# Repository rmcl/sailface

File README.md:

# SailFace

An autonomous (non-sail powered) boat thing.

# Photos

## Mark II

## Mark I

# Code organization

## Microcontroller (sailface)

Runs on an arduino MEGA. This code manages navigation, communication and power management.

## Control (sailface_control)

Python code for controling sailface remotely.

### Lambda Data Capture (lambda_data_capture)

This module is a lambda function that will receive the messages relayed from the Iridium Short-Burst Data (SBD) network via the RockBLOCK service (https://docs.rockblock.rock7.com/docs/getting-started). 

### Command Lib (sailface_command)

A python library for creating command messages that can be sent to the vessel.

### Notebooks

Various jupyter notebooks for processing KML + sending commands to the vessel.

## Schematics

PCB/Schematic Designs for an Arduino shield which connects the various electronic components. Created using KiCAD

## 3dmodels

3d models for various parts largely for supporting the internals of the vessel.

# Communication

The Arduino communicates sends messages to the Iridium Short-Burst Data services via a RockBLOCK 9603.

SailFace status messages:

### Power

```
P:<batteryVoltage>,batteryCurrentDraw,solarPanelCurrent
P:3.70,500,400
```

### Navigation/Position

```
N:<positionValid>,<latitude>,<longitude>,<speed>,<course>,<gpsFixAge>
```

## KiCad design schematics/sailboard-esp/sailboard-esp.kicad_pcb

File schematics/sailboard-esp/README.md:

Changelog
##################

Version 1.1
---------------------
* Moved towards using a buck converter from Vin to 5V and then a simple linear regulator for 5v to 3.3v

Version 1.2
------------------
* Added dampening capacitor next to servo.

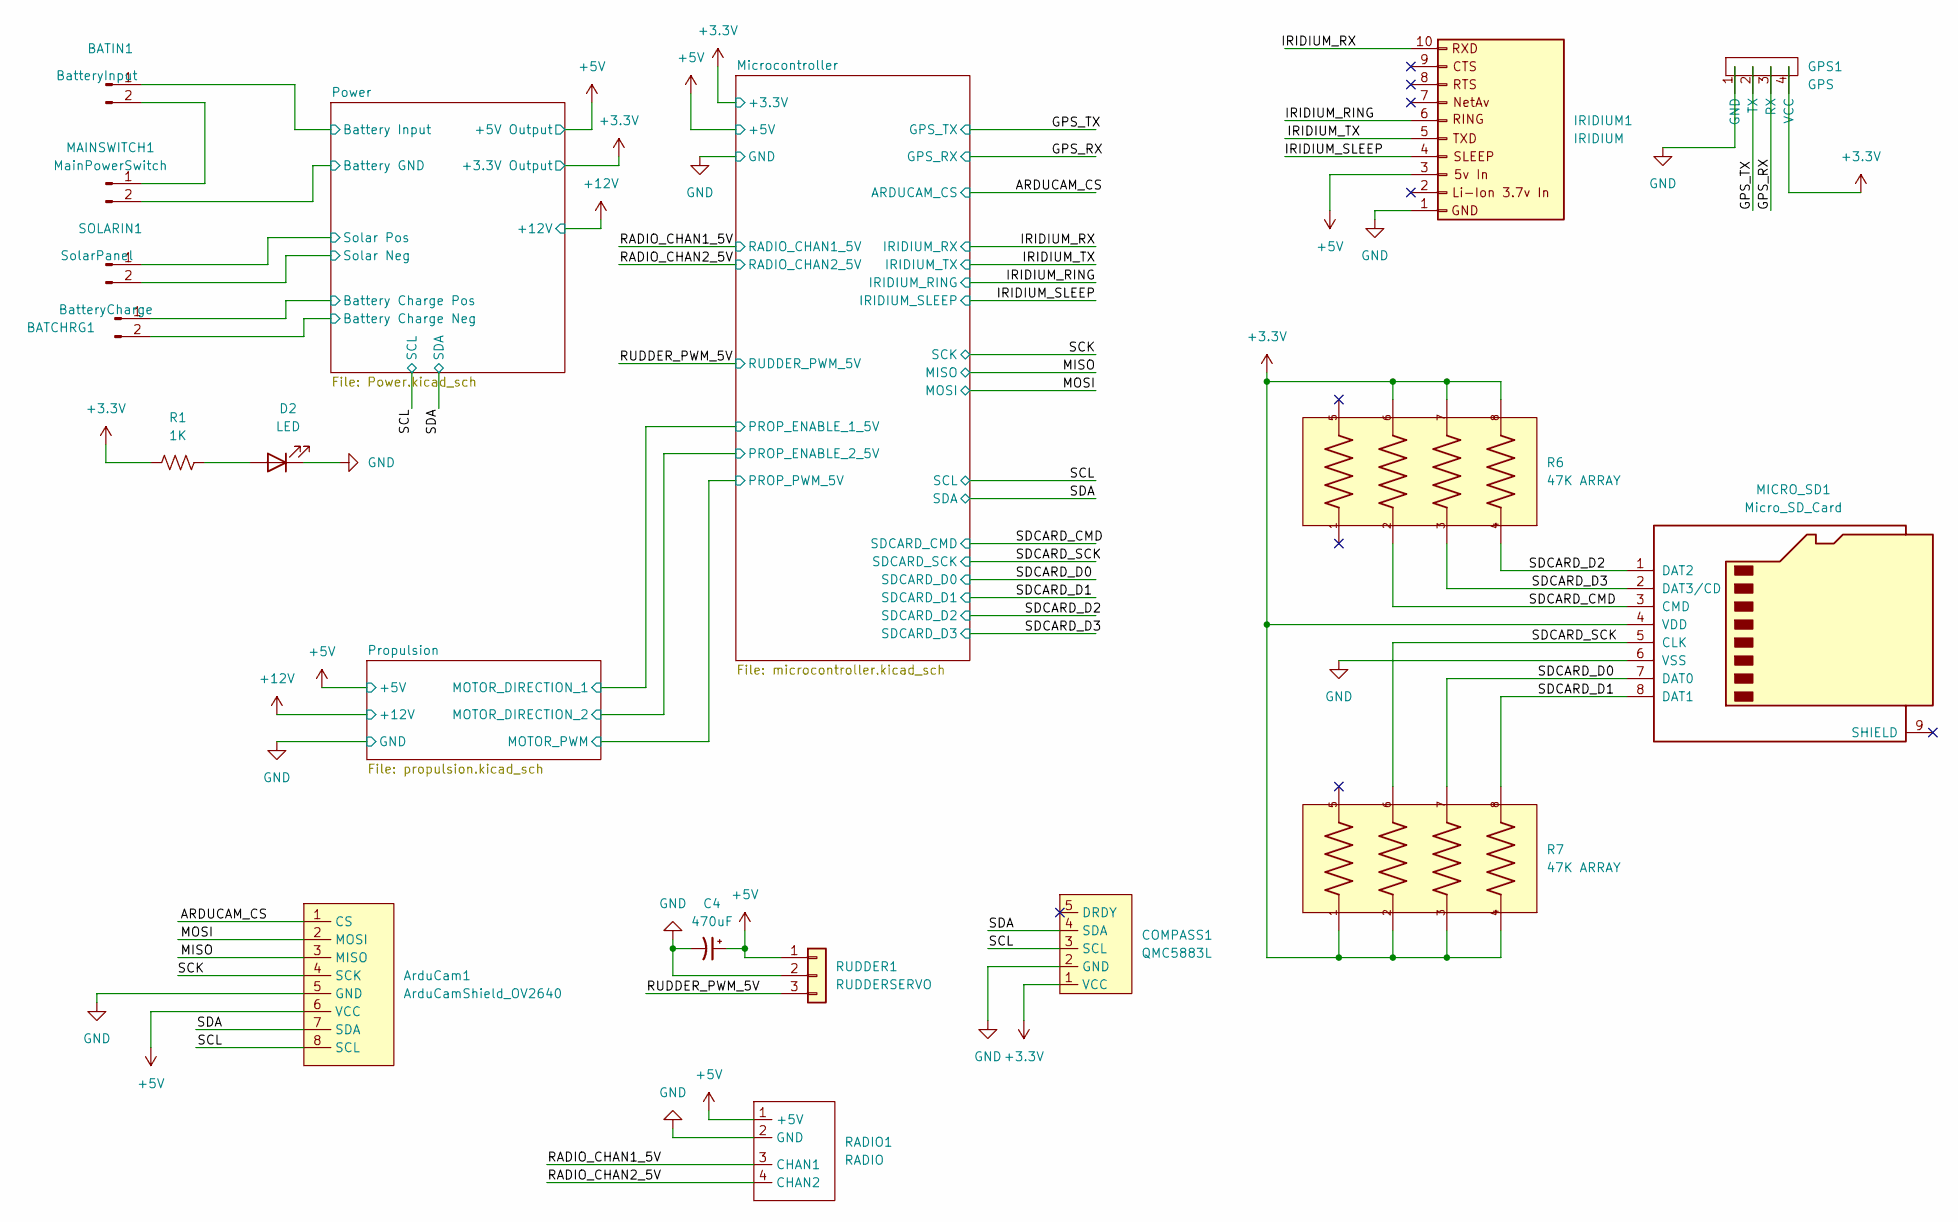
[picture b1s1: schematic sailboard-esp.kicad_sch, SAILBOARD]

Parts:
ArduCam1: ArduCamShield_OV2640; PinHeader_1x08_P2.54mm_Vertical
BATCHRG1: BatteryCharge; JST_XH_B2B-XH-A_1x02_P2.50mm_Vertical
BATIN1: BatteryInput; JST_XH_B2B-XH-A_1x02_P2.50mm_Vertical
C4: 470uF; CP_Radial_D8.0mm_P3.50mm
COMPASS1: QMC5883L; PinHeader_1x05_P2.54mm_Vertical
D2: LED; LED_0603_1608Metric
GPS1: GPS; PinHeader_1x04_P2.54mm_Vertical
IRIDIUM1: IRIDIUM; Molex_PicoBlade_53047-1010_1x10_P1.25mm_Vertical
MAINSWITCH1: MainPowerSwitch; JST_XH_B2B-XH-A_1x02_P2.50mm_Vertical
MICRO_SD1: Micro_SD_Card; microSD_HC_Molex_104031-0811
R1: 1K; R_0603_1608Metric
R6, R7: 47K ARRAY; RESCAXE80P320X160X70-8N; PARTREV 0
RADIO1: RADIO; PinHeader_1x04_P2.54mm_Vertical
RUDDER1: RUDDERSERVO; JST_XH_B3B-XH-A_1x03_P2.50mm_Vertical
SOLARIN1: SolarPanel; JST_XH_B2B-XH-A_1x02_P2.50mm_Vertical

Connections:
+3.3V: COMPASS1.1 (VCC), GPS1.4 (VCC), MICRO_SD1.4 (VDD), R1.1, R6.6, R6.7, R6.8, R7.1, R7.2, R7.3, R7.4; also elsewhere on the board
+5V: ArduCam1.6 (VCC), C4.1, IRIDIUM1.3 (5V), RADIO1.1 (+5V), RUDDER1.1; also elsewhere on the board
/ARDUCAM_CS: ArduCam1.1 (CS); also elsewhere on the board
/GPS_RX: GPS1.3 (RX)
/GPS_TX: GPS1.2 (TX); also elsewhere on the board
/IRIDIUM_RING: IRIDIUM1.6 (RING); also elsewhere on the board
/IRIDIUM_RX: IRIDIUM1.10 (RXD); also elsewhere on the board
/IRIDIUM_SLEEP: IRIDIUM1.4 (SLEEP); also elsewhere on the board
/IRIDIUM_TX: IRIDIUM1.5 (TXD); also elsewhere on the board
/MISO: ArduCam1.3 (MISO); also elsewhere on the board
/MOSI: ArduCam1.2 (MOSI); also elsewhere on the board
/Power/Battery Charge Neg: BATCHRG1.2, SOLARIN1.2
/Power/Battery Charge Pos: BATCHRG1.1; also elsewhere on the board
/Power/Battery Input: BATIN1.1; also elsewhere on the board
/Power/Solar Pos: SOLARIN1.1; also elsewhere on the board
/RADIO_CHAN1_5V: RADIO1.3 (CHAN1); also elsewhere on the board
/RADIO_CHAN2_5V: RADIO1.4 (CHAN2); also elsewhere on the board
/RUDDER_PWM_5V: RUDDER1.3; also elsewhere on the board
/SCK: ArduCam1.4 (SCK); also elsewhere on the board
/SCL: ArduCam1.8 (SCL), COMPASS1.3 (SCL); also elsewhere on the board
/SDA: ArduCam1.7 (SDA), COMPASS1.4 (SDA); also elsewhere on the board
/SDCARD_CMD: MICRO_SD1.3 (CMD), R6.2; also elsewhere on the board
/SDCARD_D0: MICRO_SD1.7 (DAT0), R7.7; also elsewhere on the board
/SDCARD_D1: MICRO_SD1.8 (DAT1), R7.8; also elsewhere on the board
/SDCARD_D2: MICRO_SD1.1 (DAT2), R6.4; also elsewhere on the board
/SDCARD_D3: MICRO_SD1.2 (DAT3/CD), R6.3; also elsewhere on the board
/SDCARD_SCK: MICRO_SD1.5 (CLK), R7.6; also elsewhere on the board
GND: ArduCam1.5 (GND), C4.2, COMPASS1.2 (GND), D2.1 (K), GPS1.1 (GND), IRIDIUM1.1 (GND), MAINSWITCH1.2, MICRO_SD1.6 (VSS), RADIO1.2 (GND), RUDDER1.2; also elsewhere on the board
unnamed: BATIN1.2, MAINSWITCH1.1
unnamed: D2.2 (A), R1.2

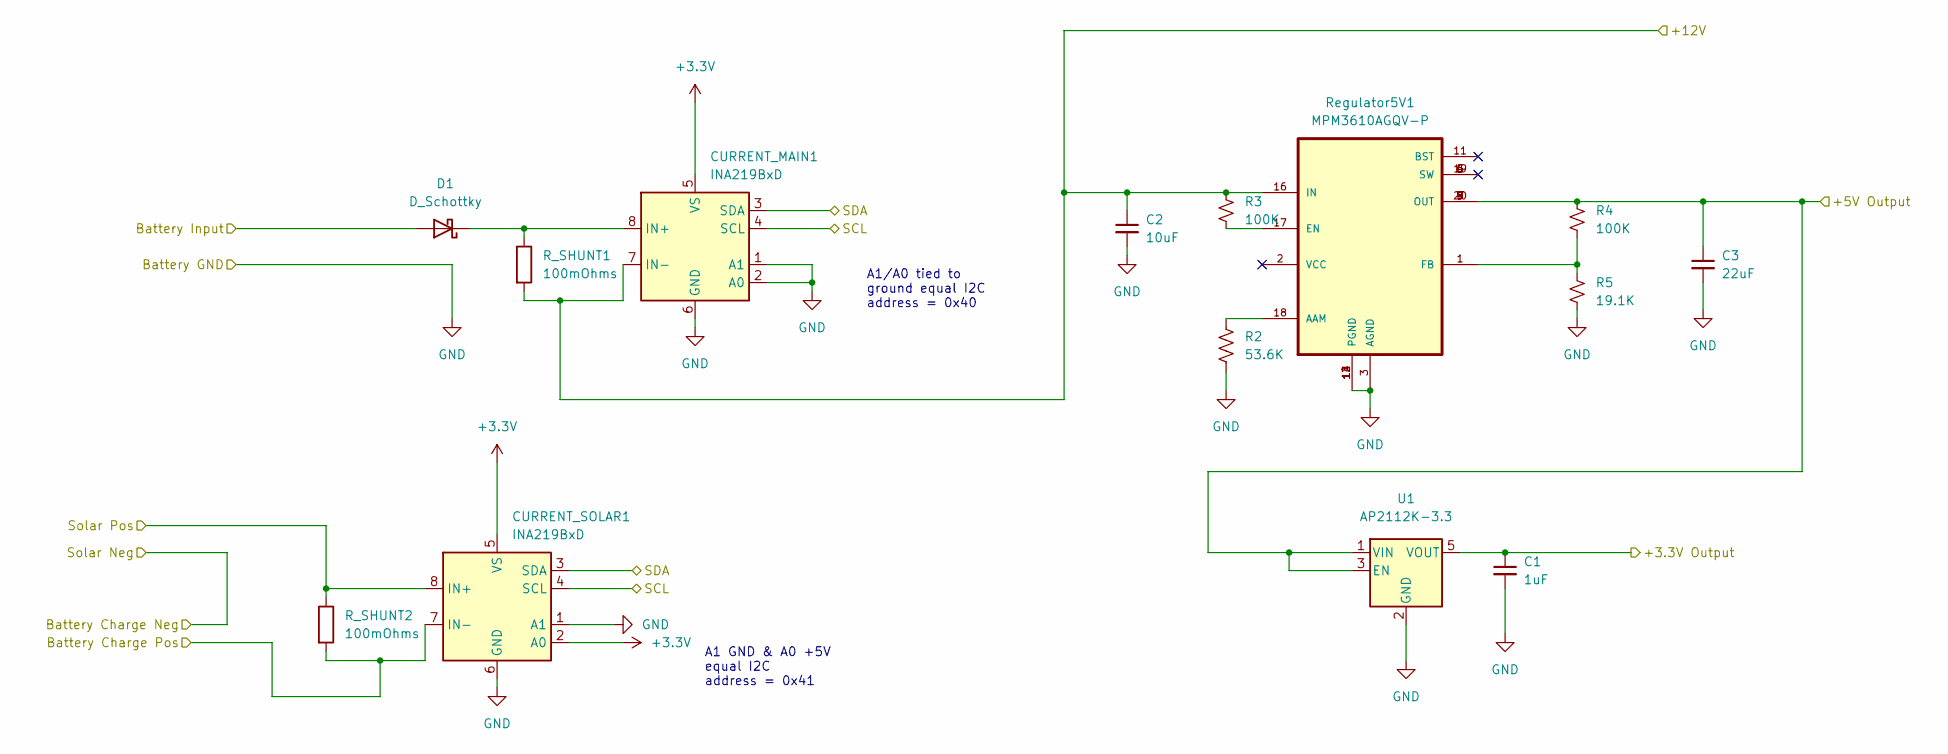
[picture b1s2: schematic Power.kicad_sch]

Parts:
C1: 1uF; C_0603_1608Metric_Pad1.08x0.95mm_HandSolder
C2: 10uF; C_0603_1608Metric_Pad1.08x0.95mm_HandSolder
C3: 22uF; C_0603_1608Metric_Pad1.08x0.95mm_HandSolder
CURRENT_MAIN1: INA219BxD; SOIC-8_3.9x4.9mm_P1.27mm
CURRENT_SOLAR1: INA219BxD; SOIC-8_3.9x4.9mm_P1.27mm
D1: D_Schottky; D_5W_P5.08mm_Vertical_AnodeUp
R2: 53.6K; R_0603_1608Metric
R3, R4: 100K; R_0603_1608Metric
R5: 19.1K; R_0603_1608Metric
R_SHUNT1, R_SHUNT2: 100mOhms; R_2512_6332Metric
Regulator5V1: MPM3610AGQV-P; MPM3620AGQV-P; PARTREV 1.0
U1: AP2112K-3.3; SOT-23-5

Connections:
+3.3V: C1.1, CURRENT_MAIN1.5 (VS), CURRENT_SOLAR1.2 (A0), CURRENT_SOLAR1.5 (VS), U1.5 (VOUT); also elsewhere on the board
+5V: C3.1, R4.1, Regulator5V1.7 (OUT), Regulator5V1.8 (OUT), Regulator5V1.9 (OUT), Regulator5V1.20 (OUT), U1.1 (VIN), U1.3 (EN); also elsewhere on the board
+12V: C2.1, CURRENT_MAIN1.7 (IN-), R3.1, R_SHUNT1.2, Regulator5V1.16 (IN); also elsewhere on the board
/Power/Battery Charge Pos: CURRENT_SOLAR1.7 (IN-), R_SHUNT2.2; also elsewhere on the board
/Power/Battery Input: D1.2 (A); also elsewhere on the board
/Power/Solar Pos: CURRENT_SOLAR1.8 (IN+), R_SHUNT2.1; also elsewhere on the board
/SCL: CURRENT_MAIN1.4 (SCL), CURRENT_SOLAR1.4 (SCL); also elsewhere on the board
/SDA: CURRENT_MAIN1.3 (SDA), CURRENT_SOLAR1.3 (SDA); also elsewhere on the board
GND: C1.2, C2.2, C3.2, CURRENT_MAIN1.1 (A1), CURRENT_MAIN1.2 (A0), CURRENT_MAIN1.6 (GND), CURRENT_SOLAR1.1 (A1), CURRENT_SOLAR1.6 (GND), R2.2, R5.2, Regulator5V1.3 (AGND), Regulator5V1.12 (PGND), Regulator5V1.13 (PGND), Regulator5V1.14 (PGND), U1.2 (GND); also elsewhere on the board
unnamed: CURRENT_MAIN1.8 (IN+), D1.1 (K), R_SHUNT1.1
unnamed: R2.1, Regulator5V1.18 (AAM)
unnamed: R3.2, Regulator5V1.17 (EN)
unnamed: R4.2, R5.1, Regulator5V1.1 (FB)

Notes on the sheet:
A1 GND & A0 +5V equal I2C address = 0x41
A1/A0 tied to ground equal I2C address = 0x40

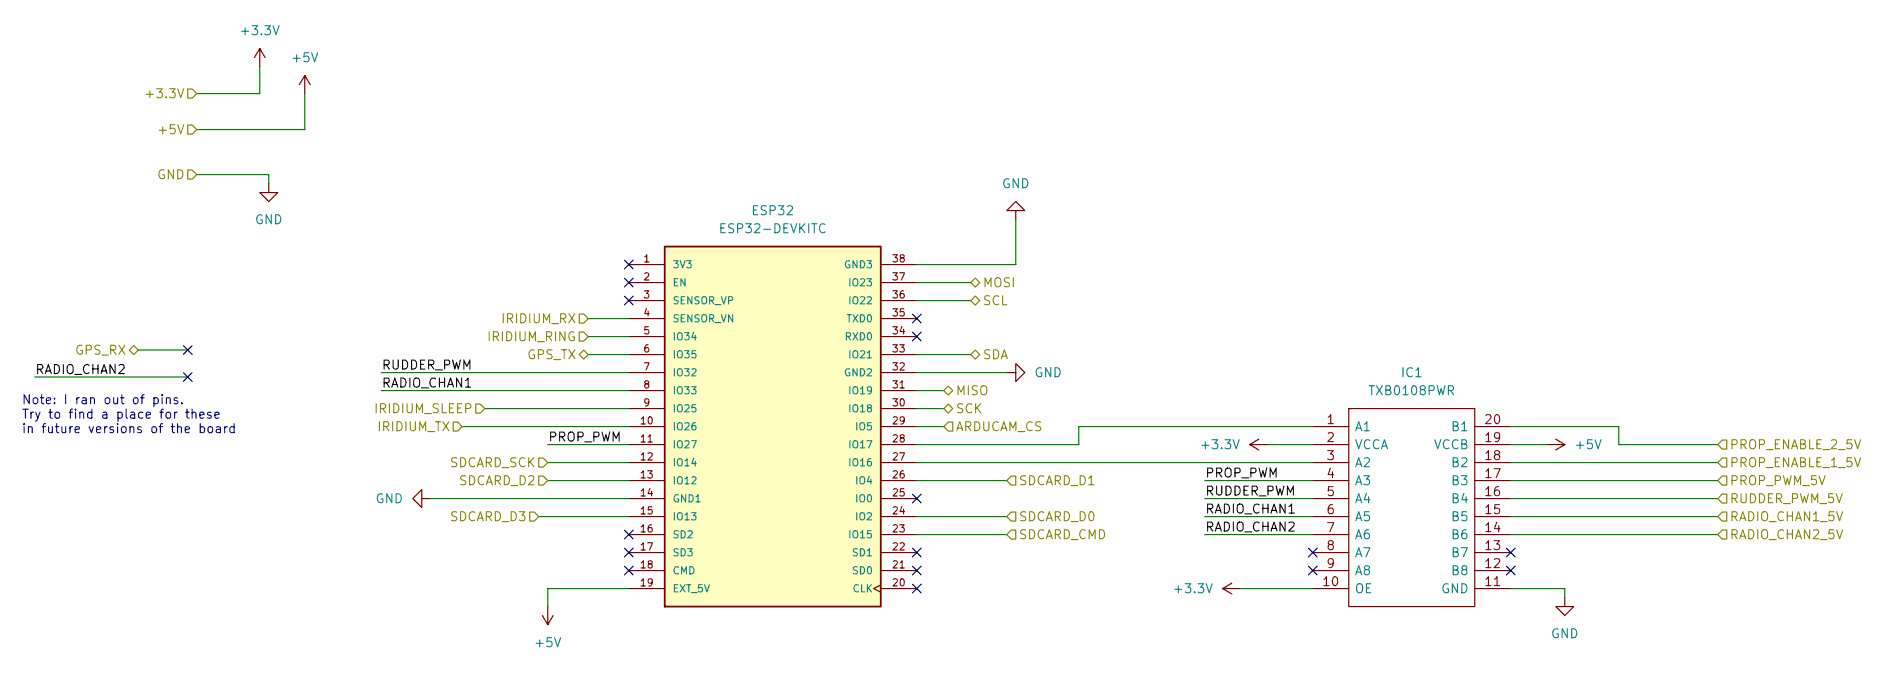
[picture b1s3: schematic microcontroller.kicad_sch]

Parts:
ESP32: ESP32-DEVKITC; MODULE_ESP32-DEVKITC-RESIZED; PARTREV N/A
IC1: TXB0108PWR; SOP65P640X120-20N; Manufacturer_Part_Number TXB0108PWR; Mouser Part Number 595-TXB0108PWR

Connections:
+3.3V: IC1.2 (VCCA), IC1.10 (OE); also elsewhere on the board
+5V: ESP32.19 (EXT_5V), IC1.19 (VCCB); also elsewhere on the board
/ARDUCAM_CS: ESP32.29 (IO5); also elsewhere on the board
/GPS_TX: ESP32.6 (IO35); also elsewhere on the board
/IRIDIUM_RING: ESP32.5 (IO34); also elsewhere on the board
/IRIDIUM_RX: ESP32.4 (SENSOR_VN); also elsewhere on the board
/IRIDIUM_SLEEP: ESP32.9 (IO25); also elsewhere on the board
/IRIDIUM_TX: ESP32.10 (IO26); also elsewhere on the board
/MISO: ESP32.31 (IO19); also elsewhere on the board
/MOSI: ESP32.37 (IO23); also elsewhere on the board
/Microcontroller/PROP_ENABLE_1_5V: IC1.18 (B2); also elsewhere on the board
/Microcontroller/PROP_ENABLE_2_5V: IC1.20 (B1); also elsewhere on the board
/Microcontroller/PROP_PWM: ESP32.11 (IO27), IC1.4 (A3)
/Microcontroller/PROP_PWM_5V: IC1.17 (B3); also elsewhere on the board
/Microcontroller/RADIO_CHAN1: ESP32.8 (IO33), IC1.6 (A5)
/Microcontroller/RADIO_CHAN2: IC1.7 (A6)
/Microcontroller/RUDDER_PWM: ESP32.7 (IO32), IC1.5 (A4)
/RADIO_CHAN1_5V: IC1.15 (B5); also elsewhere on the board
/RADIO_CHAN2_5V: IC1.14 (B6); also elsewhere on the board
/RUDDER_PWM_5V: IC1.16 (B4); also elsewhere on the board
/SCK: ESP32.30 (IO18); also elsewhere on the board
/SCL: ESP32.36 (IO22); also elsewhere on the board
/SDA: ESP32.33 (IO21); also elsewhere on the board
/SDCARD_CMD: ESP32.23 (IO15); also elsewhere on the board
/SDCARD_D0: ESP32.24 (IO2); also elsewhere on the board
/SDCARD_D1: ESP32.26 (IO4); also elsewhere on the board
/SDCARD_D2: ESP32.13 (IO12); also elsewhere on the board
/SDCARD_D3: ESP32.15 (IO13); also elsewhere on the board
/SDCARD_SCK: ESP32.12 (IO14); also elsewhere on the board
GND: ESP32.14 (GND1), ESP32.32 (GND2), ESP32.38 (GND3), IC1.11 (GND); also elsewhere on the board
unnamed: ESP32.27 (IO16), IC1.3 (A2)
unnamed: ESP32.28 (IO17), IC1.1 (A1)

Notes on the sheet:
Note: I ran out of pins. Try to find a place for these in future versions of the board

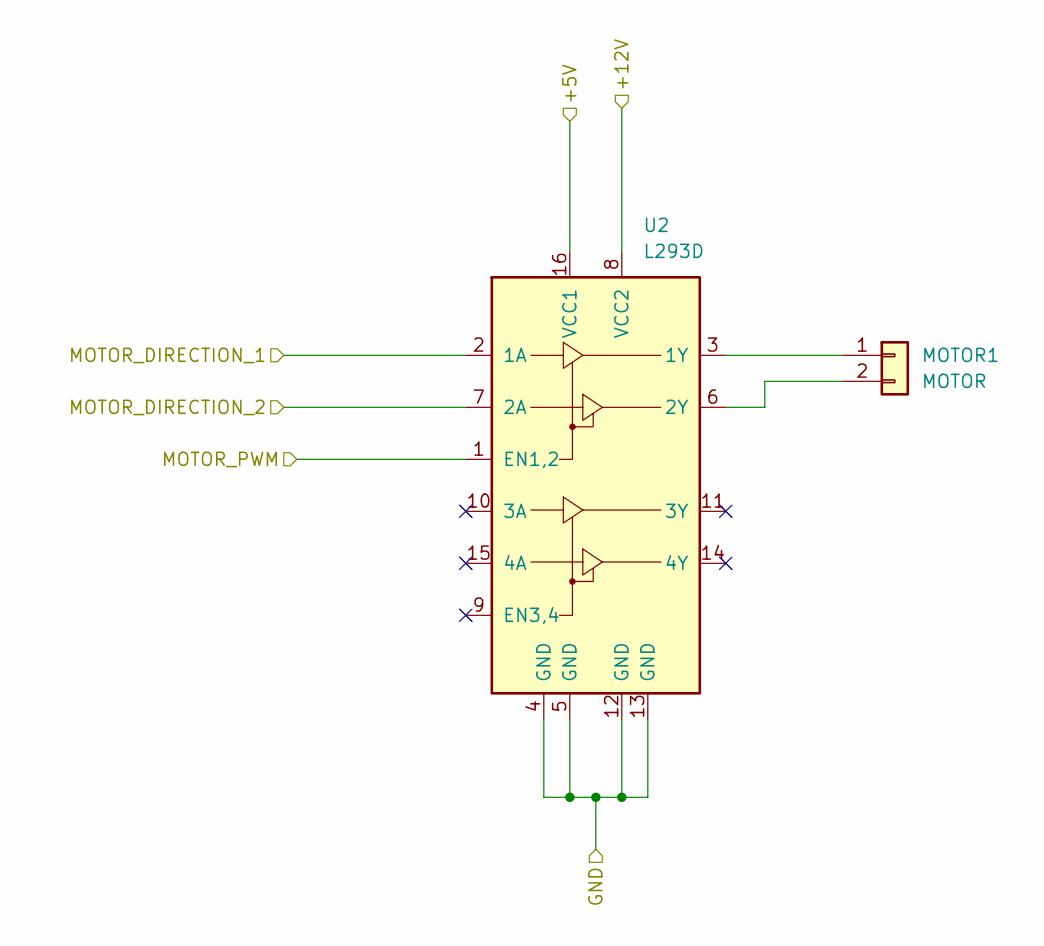
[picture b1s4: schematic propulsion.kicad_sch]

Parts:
MOTOR1: MOTOR; JST_XH_B2B-XH-A_1x02_P2.50mm_Vertical
U2: L293D; DIP-16_W7.62mm

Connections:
+5V: U2.16 (VCC1); also elsewhere on the board
+12V: U2.8 (VCC2); also elsewhere on the board
/Microcontroller/PROP_ENABLE_1_5V: U2.2 (1A); also elsewhere on the board
/Microcontroller/PROP_ENABLE_2_5V: U2.7 (2A); also elsewhere on the board
/Microcontroller/PROP_PWM_5V: U2.1 (EN1,2); also elsewhere on the board
GND: U2.4 (GND), U2.5 (GND), U2.12 (GND), U2.13 (GND); also elsewhere on the board
unnamed: MOTOR1.1, U2.3 (1Y)
unnamed: MOTOR1.2, U2.6 (2Y)

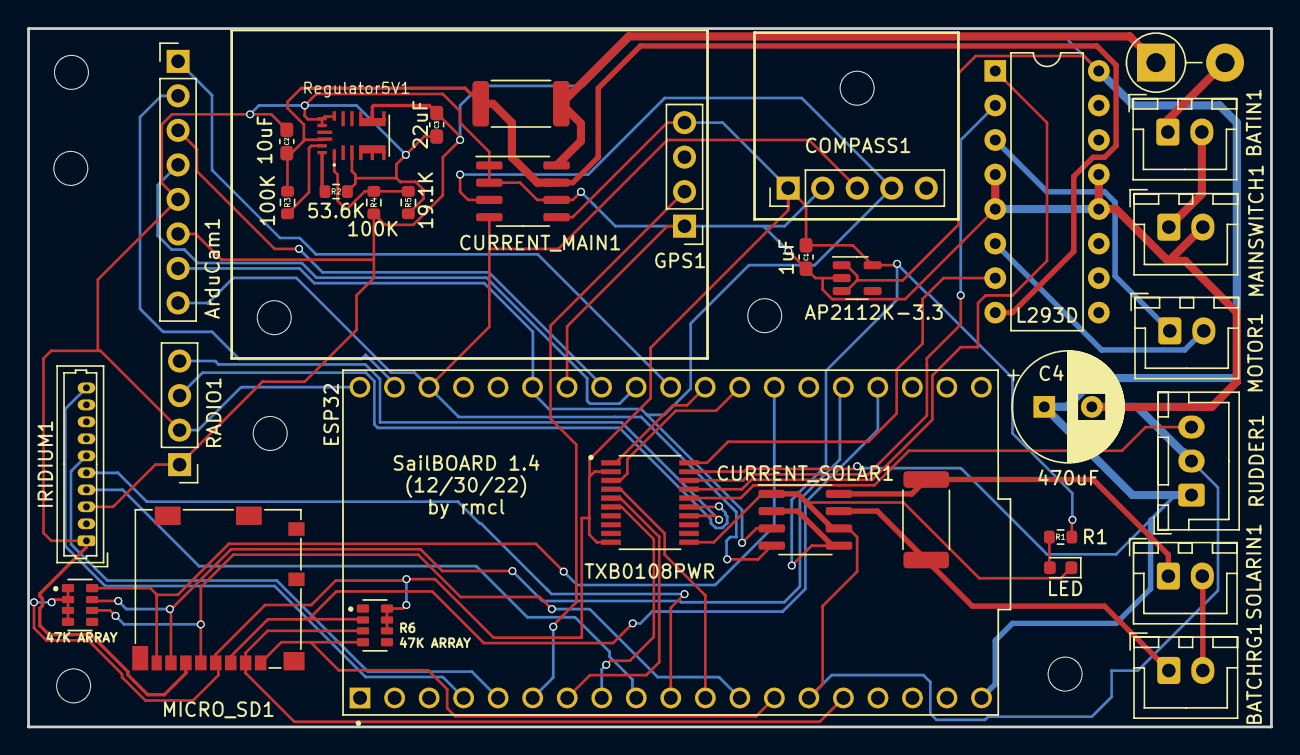
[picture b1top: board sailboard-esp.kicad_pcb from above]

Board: 2 copper layers, 91.4 x 51.4 mm, 38 parts (0 on the bottom side), 44 nets.

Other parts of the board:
H1, H1#2, H1#3, H1#4: MountingHole_2.5mm

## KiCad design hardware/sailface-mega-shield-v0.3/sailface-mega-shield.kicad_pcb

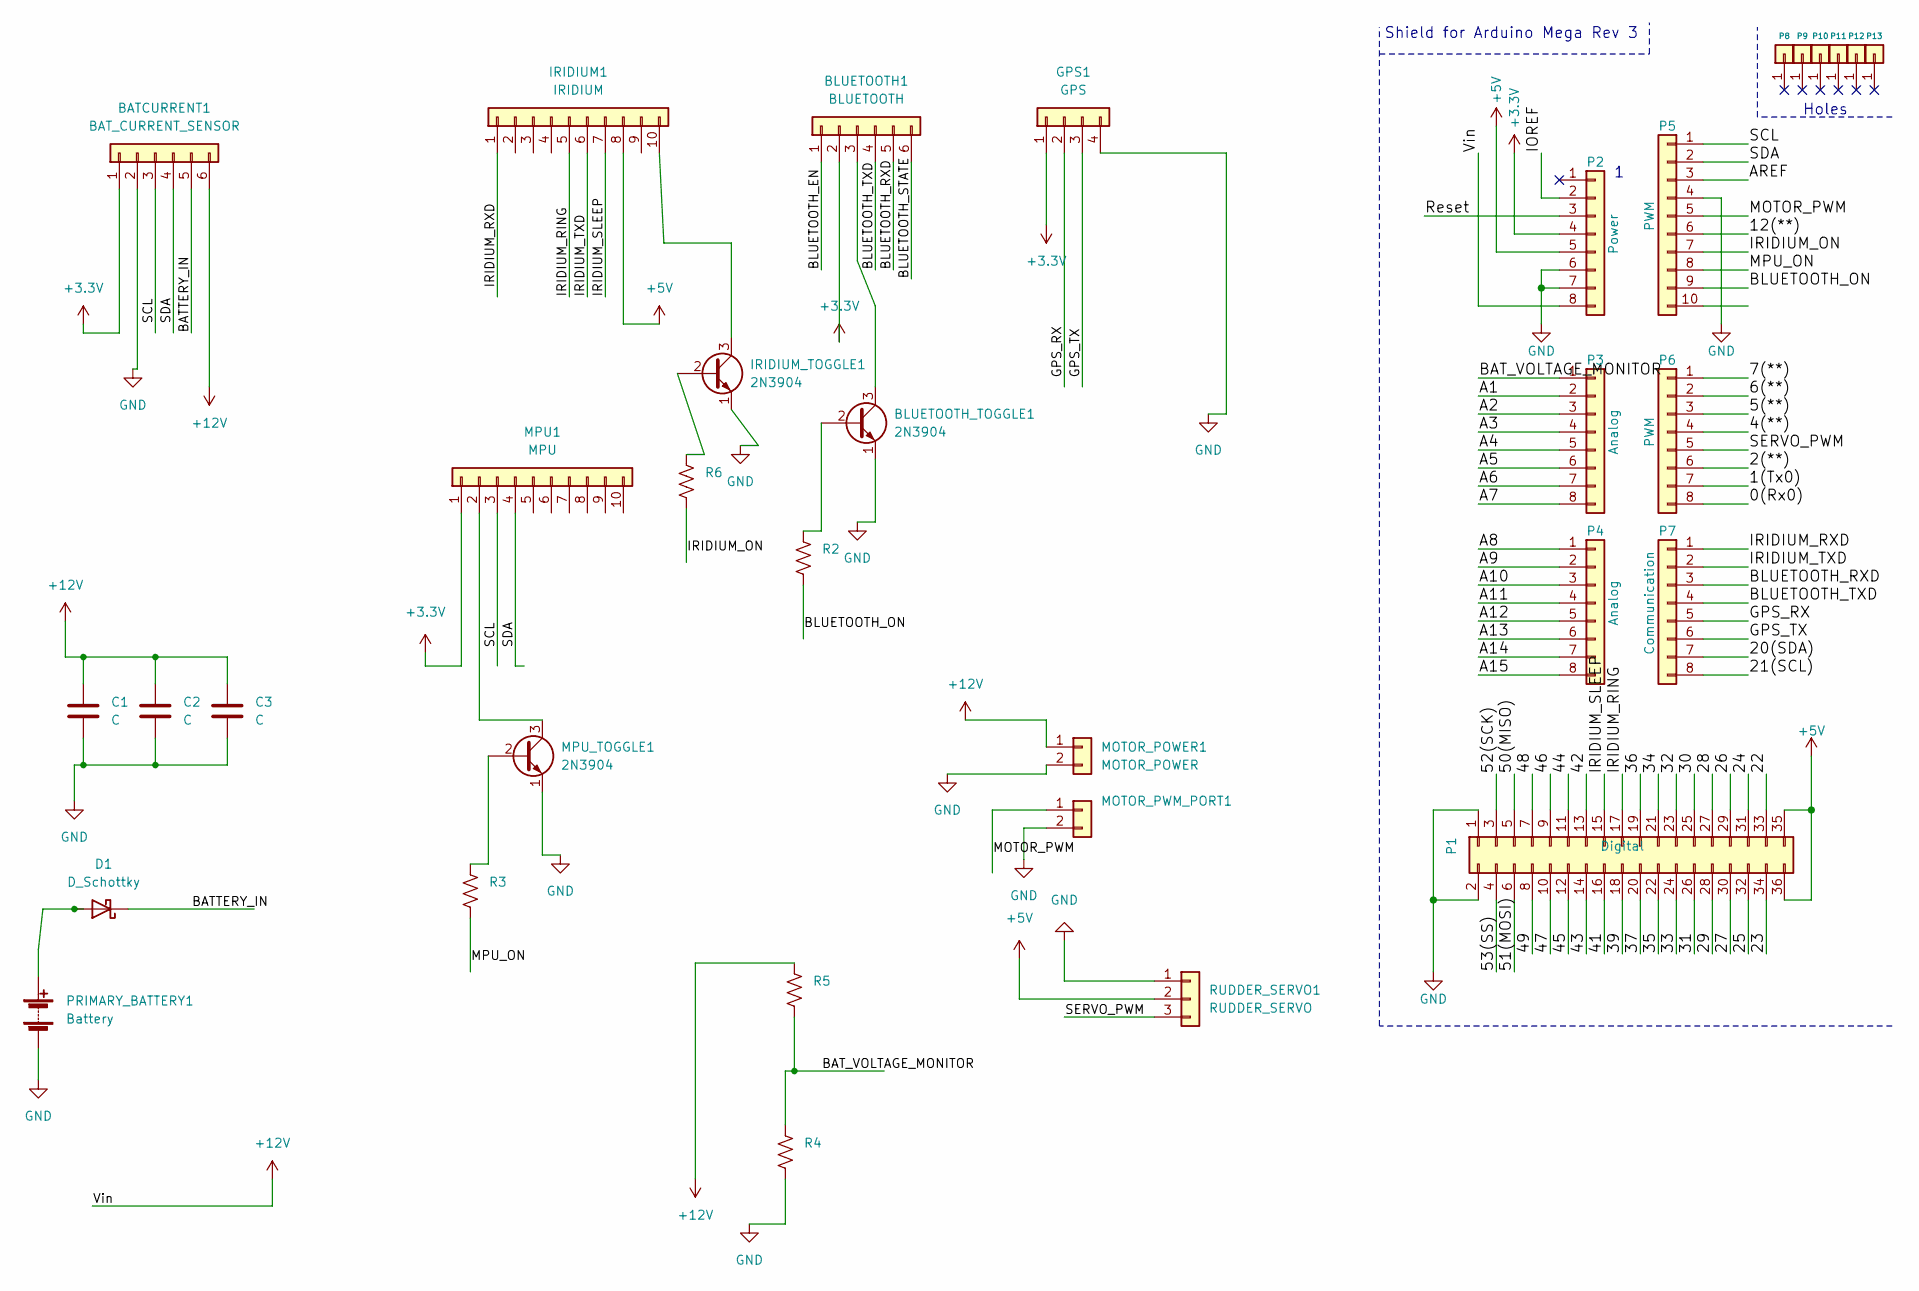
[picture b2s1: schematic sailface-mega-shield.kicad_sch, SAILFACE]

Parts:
BATCURRENT1: BAT_CURRENT_SENSOR; PinSocket_1x06_P2.54mm_Vertical
BLUETOOTH1: BLUETOOTH; PinSocket_1x06_P2.54mm_Vertical
BLUETOOTH_TOGGLE1: 2N3904; TO-92_Inline
C1, C2, C3: C; CP_Radial_D5.0mm_P2.00mm
D1: D_Schottky; D_5W_P5.08mm_Vertical_AnodeUp
GPS1: GPS; PinSocket_1x04_P2.54mm_Vertical
IRIDIUM1: IRIDIUM; PinSocket_1x10_P2.54mm_Vertical
IRIDIUM_TOGGLE1: 2N3904; TO-92_Inline
MOTOR_POWER1: MOTOR_POWER; PinSocket_1x02_P2.54mm_Vertical
MOTOR_PWM_PORT1: (no value)
MPU1: MPU; PinSocket_1x10_P2.54mm_Vertical
MPU_TOGGLE1: 2N3904; TO-92_Inline
P1: Digital; Socket_Strip_Arduino_2x18
P2: Power; Socket_Strip_Arduino_1x08
P3, P4: Analog; Socket_Strip_Arduino_1x08
P5: PWM; Socket_Strip_Arduino_1x10
P6: PWM; Socket_Strip_Arduino_1x08
P7: Communication; Socket_Strip_Arduino_1x08
P8, P9, P10, P11, P12, P13: CONN_01X01; Arduino_1pin
PRIMARY_BATTERY1: Battery; PinSocket_1x02_P2.54mm_Vertical
R2, R3, R4, R5, R6: (no value)
RUDDER_SERVO1: RUDDER_SERVO; PinSocket_1x03_P2.54mm_Vertical

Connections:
+3V3: BATCURRENT1.1, BLUETOOTH1.2, GPS1.1, MPU1.1, P2.4
+5V: IRIDIUM1.8, P1.35, P1.36, P2.5, RUDDER_SERVO1.2
+12V: BATCURRENT1.6, C1.1, C2.1, C3.1, MOTOR_POWER1.1, P2.8, R5.1; also elsewhere on the board
/0(Rx0): P6.8
/1(Tx0): P6.7
/2(**): P6.6
/4(**): P6.4
/5(**): P6.3
/6(**): P6.2
/7(**): P6.1
/12(**): P5.6
/20(SDA): P7.7
/21(SCL): P7.8
/22: P1.33
/23: P1.34
/24: P1.31
/25: P1.32
/26: P1.29
/27: P1.30
/28: P1.27
/29: P1.28
/30: P1.25
/31: P1.26
/32: P1.23
/33: P1.24
/34: P1.21
/35: P1.22
/36: P1.19
/37: P1.20
/39: P1.18
/41: P1.16
/42: P1.13
/43: P1.14
/44: P1.11
/45: P1.12
/46: P1.9
/47: P1.10
/48: P1.7
/49: P1.8
/50(MISO): P1.5
/51(MOSI): P1.6
/52(SCK): P1.3
/53(SS): P1.4
/A1: P3.2
/A2: P3.3
/A3: P3.4
/A4: P3.5
/A5: P3.6
/A6: P3.7
/A7: P3.8
/A8: P4.1
/A9: P4.2
/A10: P4.3
/A11: P4.4
/A12: P4.5
/A13: P4.6
/A14: P4.7
/A15: P4.8
/AREF: P5.3
/BATTERY_IN: BATCURRENT1.5, D1.1 (K)
/BAT_VOLTAGE_MONITOR: P3.1, R4.1, R5.2
/BLUETOOTH_EN: BLUETOOTH1.1
/BLUETOOTH_ON: P5.9, R2.2
/BLUETOOTH_RXD: BLUETOOTH1.5, P7.3
/BLUETOOTH_STATE: BLUETOOTH1.6
/BLUETOOTH_TXD: BLUETOOTH1.4, P7.4
/GPS_RX: GPS1.2, P7.5
/GPS_TX: GPS1.3, P7.6
/IOREF: P2.2
/IRIDIUM_ON: P5.7, R6.2
/IRIDIUM_RING: IRIDIUM1.5, P1.17
/IRIDIUM_RXD: IRIDIUM1.1, P7.1
/IRIDIUM_SLEEP: IRIDIUM1.7, P1.15
/IRIDIUM_TXD: IRIDIUM1.6, P7.2
/MOTOR_PWM: MOTOR_PWM_PORT1.1, P5.5; also elsewhere on the board
/MPU_ON: P5.8, R3.2
/Reset: P2.3
/SCL: BATCURRENT1.3, MPU1.3, P5.1
/SDA: BATCURRENT1.4, MPU1.4, P5.2
/SERVO_PWM: P6.5, RUDDER_SERVO1.3
GND: BATCURRENT1.2, BLUETOOTH_TOGGLE1.1 (E), C1.2, C2.2, C3.2, GPS1.4, IRIDIUM_TOGGLE1.1 (E), MOTOR_POWER1.2, MOTOR_PWM_PORT1.2, MPU_TOGGLE1.1 (E), P1.1, P1.2, P2.6, P2.7, P5.4, PRIMARY_BATTERY1.2 (-), R4.2, RUDDER_SERVO1.1; also elsewhere on the board
unnamed: BLUETOOTH1.3, BLUETOOTH_TOGGLE1.3 (C)
unnamed: BLUETOOTH_TOGGLE1.2 (B), R2.1
unnamed: D1.2 (A), PRIMARY_BATTERY1.1 (+)
unnamed: IRIDIUM1.10, IRIDIUM_TOGGLE1.3 (C)
unnamed: IRIDIUM_TOGGLE1.2 (B), R6.1
unnamed: MPU1.2, MPU_TOGGLE1.3 (C)
unnamed: MPU_TOGGLE1.2 (B), R3.1

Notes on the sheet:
Holes
Shield for Arduino Mega Rev 3

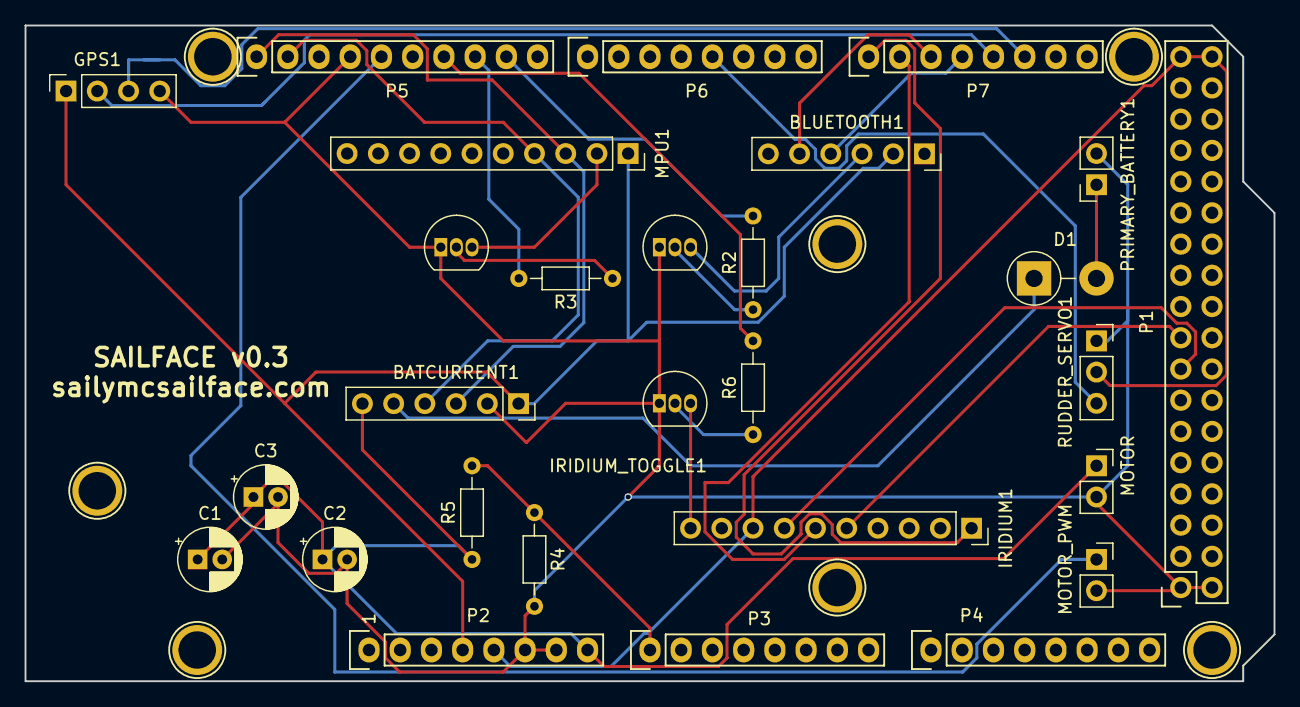
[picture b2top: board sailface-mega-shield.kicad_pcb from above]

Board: 2 copper layers, 101.6 x 53.3 mm, 35 parts (0 on the bottom side), 28 nets.

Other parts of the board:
MOTOR: MOTOR_POWER; PinSocket_1x02_P2.54mm_Vertical
MOTOR_PWM: MOTOR_PWM_PORT; PinSocket_1x02_P2.54mm_Vertical
P11#2: CONN_01X01; Arduino_1pin

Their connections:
+12V: MOTOR.1; also elsewhere on the board
/MOTOR_PWM: MOTOR_PWM.1; also elsewhere on the board
GND: MOTOR.2, MOTOR_PWM.2; also elsewhere on the board

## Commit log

2020-07-16 initial commit.
2020-07-16 added requirements file.
2020-07-17 added helm control module.
2020-08-03 commit some stuff.
2020-08-06 progress.
2020-08-06 improved readme.
2020-08-06 added scripts for running control as a systemd service.
2020-08-20 added makefile.
2020-08-20 add libs to makefile.
2020-08-20 improved makefile to install required libs.
2020-08-20 added clean statement.
2020-08-20 move sailface control install to makefile.
2020-08-20 added solar power current INA219.
2020-09-07 added propulsion module for driving main prop.
2021-01-03 tmp commit.
2021-12-24 progress from pi.
2021-12-24 remove bad files.
2021-12-24 completed first commands.
2021-12-29 lots of progress.
2021-12-31 lots of changes.
2022-01-07 added logic for voltage divider.
2022-01-15 initial commit of lambda functions for processing sailface messages.
2022-01-15 tweak example vals.
2022-01-15 got distance and bearing to waypoint working.
2022-06-20 update code.
2022-06-20 add control.
2022-06-20 added megashield kicad files.
2022-07-11 added motor and motor holder model.
2022-07-11 vertical assembly and battery holder.
2022-07-18 progress
2022-07-19 current state.
2022-07-19 circuit board.
2022-07-22 progress and renamed hardward to schematics.
2022-07-22 add 3d models.
2022-07-22 moving things around a bit.
2022-07-22 move requirements to live with python files.
2022-07-22 update readme.
2022-07-28 refactor
2022-07-28 building out bluetooth command module.
2022-07-30 progress on iridium and main loop refactor.
2022-08-03 progress debugging iridium.
2022-08-03 fix typo.
2022-08-03 remove old debug code.
2022-08-04 tweaks to get iridium transmit working.
2022-08-04 fix tab.
2022-08-04 remove commented out code.
2022-08-04 move bluetooth configure code out of sailforce device folder.
2022-08-04 add readme.
2022-08-04 progress on testing cloud functions.
2022-08-04 add docker compose for local testing.
2022-08-05 added persist data manager.
2022-08-07 finally got a test runner sort of working.
2022-08-07 added readme.
2022-08-18 improve persisted data.
2022-08-18 tweak position to fix mpu.
2022-08-18 save some 3d models.
2022-08-18 add an example related to running to mpu.
2022-08-23 tweaking cloud function.
2022-08-23 fixed cloud function.
2022-08-24 update content type of s3 file.
2022-08-28 progress on MPU, sat transmit.
2022-08-28 remove old file.
2022-09-02 update navigation and iridium to receive waypoint commands.
2022-09-02 refactor codebase to treat sailface as a library that can be imported by test sketches.
2022-10-08 refactor position to use HMC5883 rather than accelerometer
2022-10-09 typo.
2022-10-09 working on code to build commands to transmit via iridium.
2022-10-15 restructured repo so that all the control software is in a subdir
2022-10-15 refactor.
2022-10-15 move status parser into lib.
2022-10-15 added tests.
2022-10-17 added readme for frontend folder.
2022-10-23 tweaks.
2022-10-25 tweak front end.
2022-11-01 progress on something.
2022-11-13 version 1.0.
2022-11-13 add version to silkscreen.
2022-11-23 v1.1 of sailboard.
2022-11-26 version 1.1.
2022-12-07 add capacitor footprint.
2022-12-09 move to version 1.2.
2022-12-11 additional tweaks to version 1.2.
2022-12-11 more tweaks. Add mounting holes for rockblock.
2022-12-14 added changelog and tweaks.
2022-12-23 v1.3.
2022-12-30 rearrange pins to avoid ESP32 reserved / wonky pins.
2022-12-30 tweaks to power.
2023-01-13 remove c++ code to make room for new micropython ondevice.
2023-01-13 removed arduino c++ examples.
2023-01-16 fix test.
2023-01-16 fixed loop using timer.
2023-01-21 curent state.
